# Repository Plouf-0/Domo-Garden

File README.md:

# Domo-Garden
#### A projet to add domotique in my garden

## 1. Project overview

#### Objective
Design and develop a Zigbee-based sensor network. The network will collect data from various environmental sensors (Thermal, Humidity, PH, ...), communicate wirelessly via Zigbee, and transmit data to a central hub that sends the information to a Home Assistant server via Wi-Fi. The system will also control an electrovalve based on predefined conditions.

#### Key Components:

- ESP32 + Zigbee module for Hub with Wi-Fi connectivity
- EFR32MG22-based sensor nodes
- Temperature, humidity sensors, and other IoT peripherals
- Electrovalve for irrigation control

## 2. Technical Specifications

#### Functional Requirements

    Data Collection: Periodic collection of temperature, humidity, and other sensor data.

    Communication: Use Zigbee for sensor node communication and Wi-Fi for sending data to the server.

    Control: Triggering of an electrovalve based on time or sensor data.

    Hub Features: The hub will aggregate data from up to 30 Zigbee devices and relay it via Wi-Fi to a server.

    Data Transfer Rate: Sensor data will be transmitted periodically, adjustable from 1 minute to 1 hour.

#### Hardware Specifications

    Microcontroller:
        ESP32
        EFR32MG22E224F512IM32

    Power Supply: Battery-powered nodes, possible use of solar panels. Minimum 1-month battery life without recharging. A 1000mAh = 1 year of battery life.

    Radio Frequency: Zigbee protocol.

    Communication Range: Up to 100 meters from hub, with a mesh network to cover distances up to 20 meters between each module.

    Sensors:
        Temperature sensors.
        Humidity sensors.
        Soil moisture sensors.
        Light sensors.
        PH sensors.
        More to come.

#### Software Specifications

    Programming Languages: C/C++ (for embedded systems), Python (for server-side automation).

    Development Environment: Simplicity Studio (for EFR32MG22).
    
    Protocols:
        Zigbee (3.0)
        Wi-Fi for hub (ESP32 or similar)
        MQTT (for data transmission to Home Assistant server).

    Operating System: FreeRTOS (for efficient power management).

#### Performance Metrics

    Battery Life: Minimum 30 days.

    Latency: Data transmission delay < 2 seconds between sensor reading and hub reception.

    Network Coverage: 100-meter total coverage using mesh networking.

## 3. Project Plan

#### Phases of Development

    Phase 1: Requirements Gathering & Research
        Gather requirements for sensors, control mechanisms, and networking.
        Research hardware options, compatibility with Zigbee and Home Assistant.

    Phase 2: Software Development
        Develop firmware for the EFR32MG22E224F512IM40 to read sensors, communicate via Zigbee, and send commands to the electrovalve with the EFR32xG22E Explorer Kit.
        Develop software for the Zigbee hub to manage data collection and Wi-Fi transmission to Home Assistant with the ESP32 and the Zigbee CC2530 Development Board.

    Phase 2^2: Hardware Design
        Design the PCB for sensor nodes (powered by EFR32MG22E224F512IM40).
        Create a schematic for power management (battery, solar charging).
        Select components for the electrovalve control system.
        Design and print the casing.

    Phase 3: Integration with Home Assistant
        Set up the Home Assistant server with Zigbee2MQTT or ZHA.
        Implement data visualization for sensor data.
        Test commands sent from Home Assistant to control the electrovalve.

    Phase 4: Prototyping
        Assemble and test initial sensor nodes and hub.
        Perform range and battery life tests.
        Ensure proper communication between the Zigbee nodes and the hub.

    Phase 6: Field Testing
        Deploy the system in a real environment (garden, yard).
        Monitor sensor performance, network stability, and control system reliability.

    Phase 6: Finalization & Documentation
        Finalize the design based on testing results.
        Prepare full documentation, including schematics, software, and user guide.

## 4. Risk Assessment

    Power Supply Issues: If solar panels are used, energy harvesting efficiency must be tested under various weather conditions.
    Connectivity Range: Trees and obstacles could interfere with Zigbee signals. Extensive field testing will be necessary to determine optimal node placement.
    Data Security: Implement encryption for data transmitted via Zigbee to prevent unauthorized access.
    Component Availability: Verify the supply chain for key components (e.g., EFR32MG22) to avoid potential delays due to shortages.

## 5. Additional Considerations

    OTA (Over-The-Air) Firmware Updates: Consider adding functionality for future remote firmware updates.
    Scalability: Keep flexibility in mind for expanding the network or adding more nodes later.

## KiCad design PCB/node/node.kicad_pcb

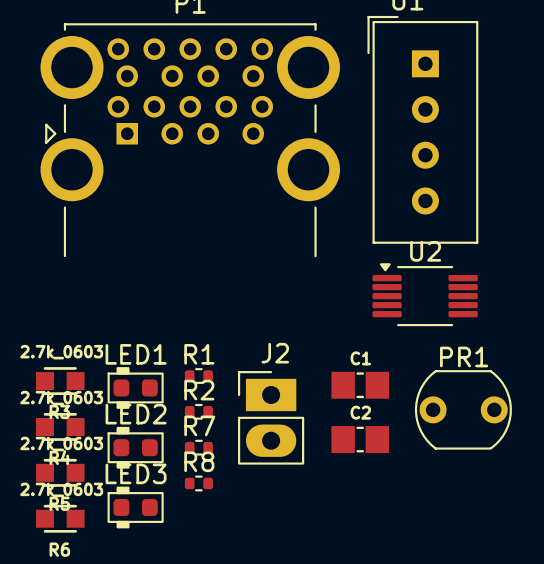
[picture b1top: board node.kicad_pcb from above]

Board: 2 copper layers, 18 parts (0 on the bottom side), 12 nets, no tracks yet.

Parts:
C1, C2: 10uF 6.3V; CAPC2012X70
J2: BATT; PinHeader_1x02_P2.54mm_Vertical
LED1: LED_0603_Green; LED_0603_1608Metric
LED2: LED_0603_Yellow; LED_0603_1608Metric
LED3: LED_0603_Red; LED_0603_1608Metric
P1: USB_C_Plug_USB2.0; USB3_A_Molex_48406-0001_Horizontal_Stacked
PR1: R_LDR_5.1x4.3mm_P3.4mm_Vertical
R1, R2, R7, R8: 10k_0402; R_0402_1005Metric
R3, R4, R5, R6: 2.7k_0603; R_0603
U1: DHT22; Aosong_DHT11_5.5x12.0_P2.54mm
U2: MCP73833-xxx-UN; MSOP-10_3x3mm_P0.5mm

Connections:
+3.3V: C2.1, J2.1, R1.1, R2.1, U1.1 (VDD), U2.9 (V_{BAT}), U2.10 (V_{BAT})
DHT GPIO: R1.2, U1.2 (DATA)
GND: C1.2, C2.2, J2.2, R6.2, R7.1, R8.1, U1.4 (GND), U2.5 (V_{SS})
unnamed: C1.1, LED1.2 (A), LED2.2 (A), LED3.2 (A), U2.1 (V_{DD}), U2.2 (V_{DD})
unnamed: LED1.1 (K), R3.1
unnamed: LED2.1 (K), R4.1
unnamed: LED3.1 (K), R5.1
unnamed: R6.1, R7.2, U2.6 (PROG)
unnamed: R4.2, U2.3 (STAT1)
unnamed: R3.2, U2.4 (STAT2)
unnamed: R8.2, U2.8 (THERM)
unnamed: R5.2, U2.7 (~PG)

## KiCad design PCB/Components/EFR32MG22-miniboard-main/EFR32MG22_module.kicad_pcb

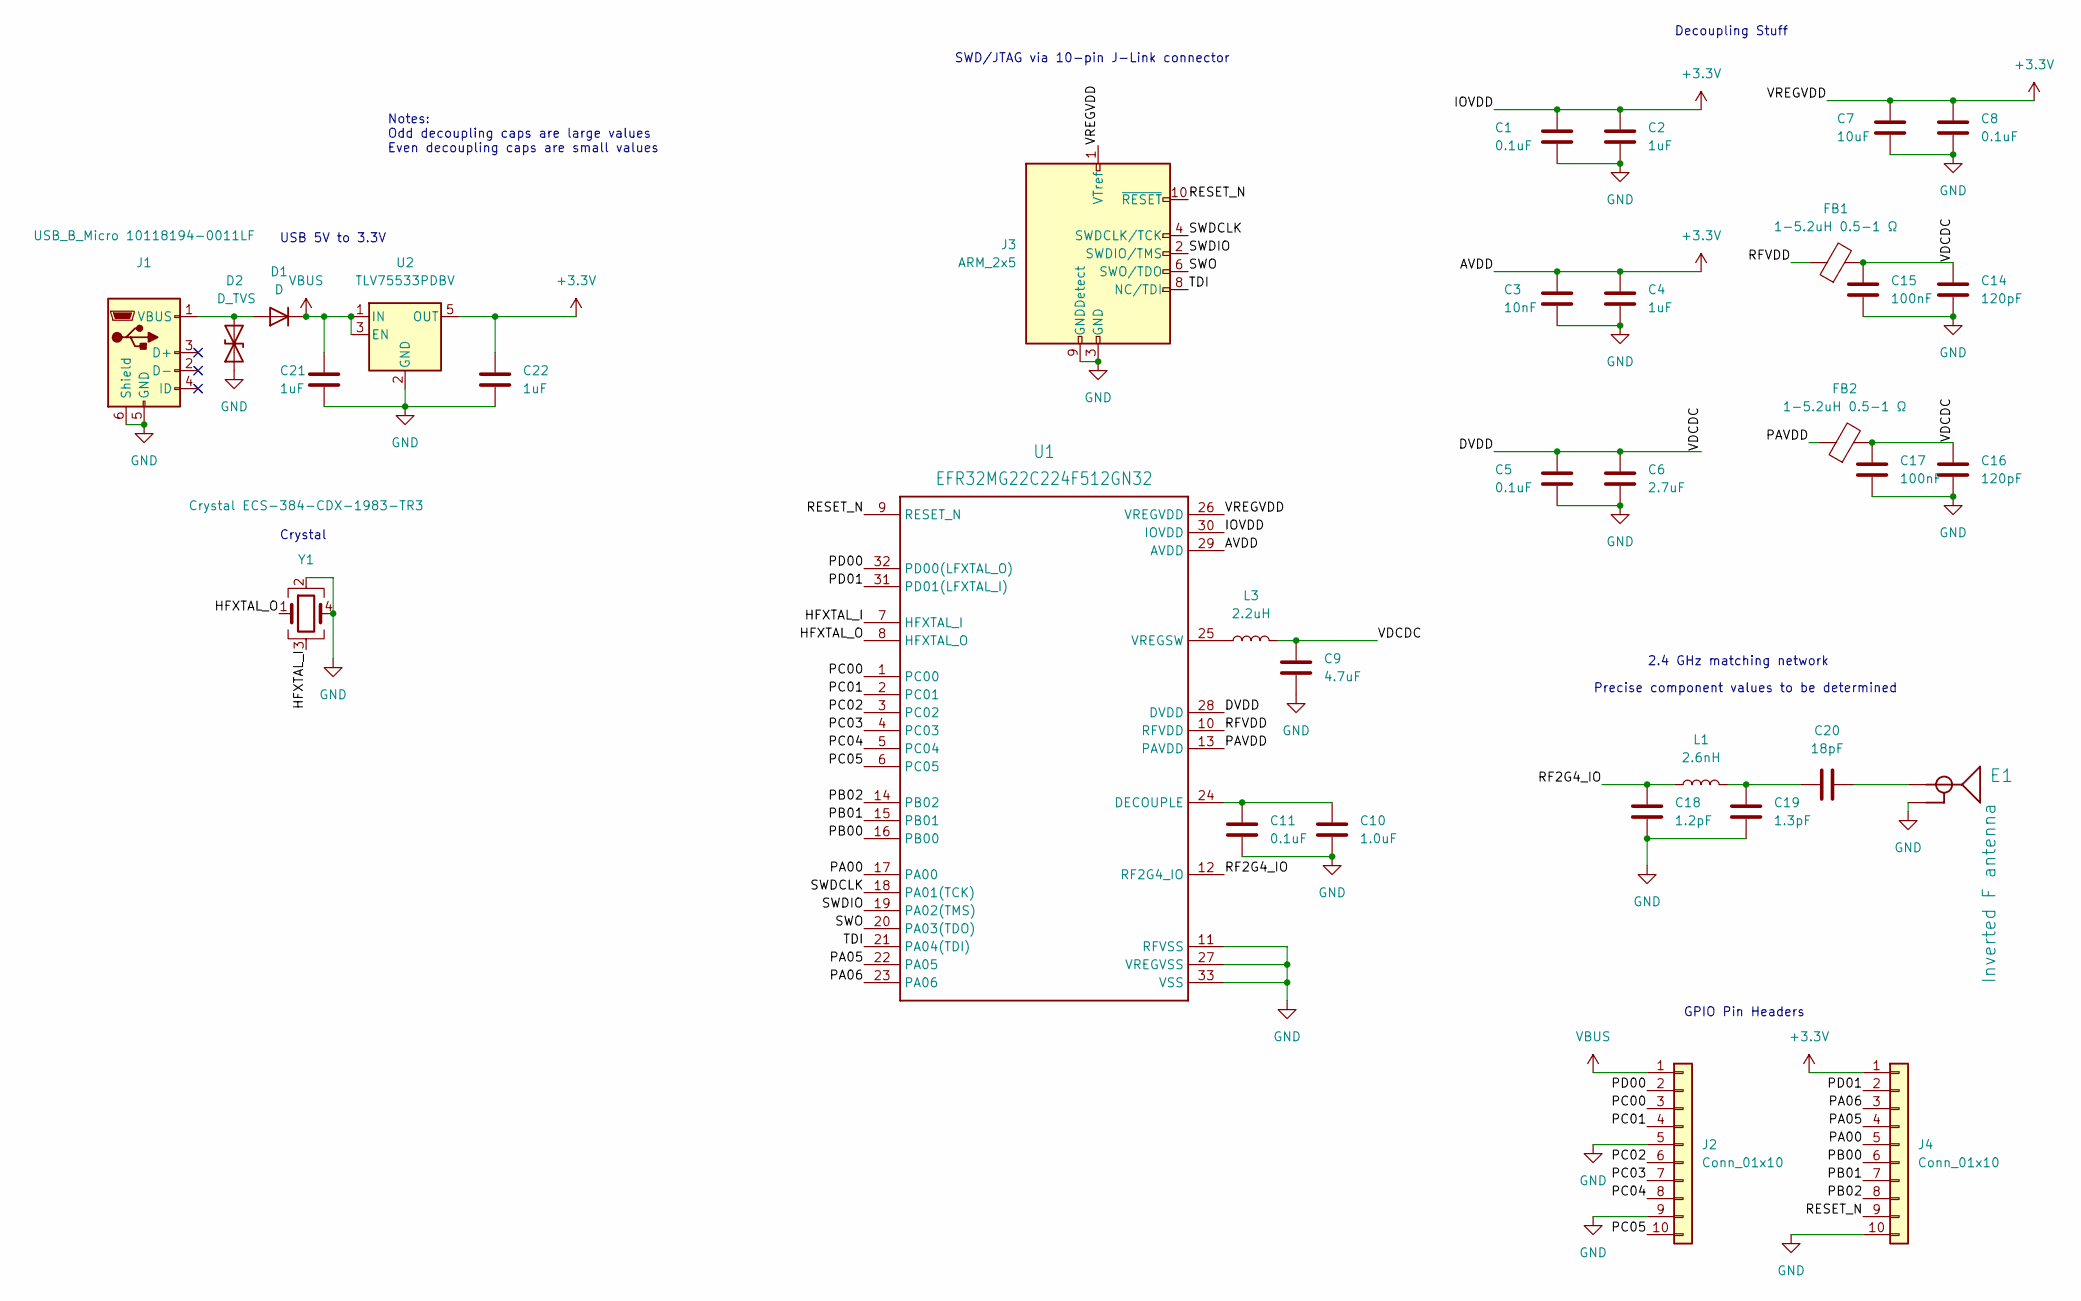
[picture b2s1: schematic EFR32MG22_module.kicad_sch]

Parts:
C1, C5, C8, C11: 0.1uF; C_0603_1608Metric_Pad1.08x0.95mm_HandSolder
C2, C4, C21, C22: 1uF; C_0603_1608Metric_Pad1.08x0.95mm_HandSolder
C3: 10nF; C_0603_1608Metric_Pad1.08x0.95mm_HandSolder
C6: 2.7uF; C_0603_1608Metric_Pad1.08x0.95mm_HandSolder
C7: 10uF; C_0603_1608Metric_Pad1.08x0.95mm_HandSolder
C9: 4.7uF; C_0603_1608Metric_Pad1.08x0.95mm_HandSolder
C10: 1.0uF; C_0603_1608Metric_Pad1.08x0.95mm_HandSolder
C14, C16: 120pF; C_0603_1608Metric_Pad1.08x0.95mm_HandSolder
C15, C17: 100nF; C_0603_1608Metric_Pad1.08x0.95mm_HandSolder
C18: 1.2pF; C_0603_1608Metric_Pad1.08x0.95mm_HandSolder
C19: 1.3pF; C_0603_1608Metric_Pad1.08x0.95mm_HandSolder
C20: 18pF; C_0603_1608Metric_Pad1.08x0.95mm_HandSolder
D1: D; D_SOD-123
D2: D_TVS; D_0201_0603Metric
E1: Inverted F antenna; TRACE_ANTENNA_2.4GHZ_15.2MM
FB1, FB2: 1-5.2uH 0.5-1 Ω; L_0603_1608Metric_Pad1.05x0.95mm_HandSolder
J1: USB_B_Micro 10118194-0011LF; USB_Micro-B_Amphenol_10118194_Horizontal
J2, J4: Conn_01x10; PinHeader_1x10_P2.54mm_Vertical
J3: ARM_2x5; 322010030000TR
L1: 2.6nH; L_0603_1608Metric_Pad1.05x0.95mm_HandSolder
L3: 2.2uH; L_0805_2012Metric_Pad1.15x1.40mm_HandSolder
U1: EFR32MG22C224F512GN32; QFN-32-1EP_4x4mm_P0.4mm_EP2.9x2.9mm_ThermalVias
U2: TLV75533PDBV; SOT-23-5
Y1: Crystal ECS-384-CDX-1983-TR3; Crystal_SMD_2016-4Pin_2.0x1.6mm

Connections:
+3.3V: C1.1, C2.1, C3.1, C4.1, C7.1, C8.1, C22.2, J3.1 (VTref), J4.1, U1.26 (VREGVDD), U1.29 (AVDD), U1.30 (IOVDD), U2.5 (OUT)
/DVDD: C5.1, C6.1, C9.1, C14.1, C15.1, C16.1, C17.1, FB1.2, FB2.2, L3.2, U1.28 (DVDD)
/HFXTAL_I: U1.7 (HFXTAL_I), Y1.3
/HFXTAL_O: U1.8 (HFXTAL_O), Y1.1
/PA00: J4.5, U1.17 (PA00)
/PA05: J4.4, U1.22 (PA05)
/PA06: J4.3, U1.23 (PA06)
/PAVDD: FB2.1, U1.13 (PAVDD)
/PB00: J4.6, U1.16 (PB00)
/PB01: J4.7, U1.15 (PB01)
/PB02: J4.8, U1.14 (PB02)
/PC00: J2.3, U1.1 (PC00)
/PC01: J2.4, U1.2 (PC01)
/PC02: J2.6, U1.3 (PC02)
/PC03: J2.7, U1.4 (PC03)
/PC04: J2.8, U1.5 (PC04)
/PC05: J2.10, U1.6 (PC05)
/PD00: J2.2, U1.32 (PD00(LFXTAL_O))
/PD01: J4.2, U1.31 (PD01(LFXTAL_I))
/RESET_N: J3.10 (~RESET), J4.9, U1.9 (RESET_N)
/RF2G4_IO: C18.1, L1.1, U1.12 (RF2G4_IO)
/RFVDD: FB1.1, U1.10 (RFVDD)
/SWDCLK: J3.4 (SWDCLK/TCK), U1.18 (PA01(TCK))
/SWDIO: J3.2 (SWDIO/TMS), U1.19 (PA02(TMS))
/SWO: J3.6 (SWO/TDO), U1.20 (PA03(TDO))
/TDI: J3.8 (NC/TDI), U1.21 (PA04(TDI))
GND: C1.2, C2.2, C3.2, C4.2, C5.2, C6.2, C7.2, C8.2, C9.2, C10.2, C11.2, C14.2, C15.2, C16.2, C17.2, C18.2, C19.2, C21.1, C22.1, D2.1 (A1), E1.GND, J1.5 (GND), J1.6 (Shield), J2.5, J2.9, J3.3 (GND), J3.5 (GND), J3.9 (GNDDetect), J4.10, U1.11 (RFVSS), U1.27 (VREGVSS), U1.33 (VSS), U2.2 (GND), Y1.2, Y1.4
unnamed: C10.1, C11.1, U1.24 (DECOUPLE)
unnamed: C19.1, C20.2, L1.2
unnamed: C20.1, E1.ANT (SIGNAL)
unnamed: D1.2 (A), D2.2 (A2), J1.1 (VBUS)
unnamed: L3.1, U1.25 (VREGSW)
VBUS: C21.2, D1.1 (K), J2.1, U2.1 (IN), U2.3 (EN)

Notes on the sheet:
GPIO Pin Headers
Precise component values to be determined
Notes: Odd decoupling caps are large values Even decoupling caps are small values
2.4 GHz matching network
SWD/JTAG via 10-pin J-Link connector
Crystal
Decoupling Stuff
USB 5V to 3.3V

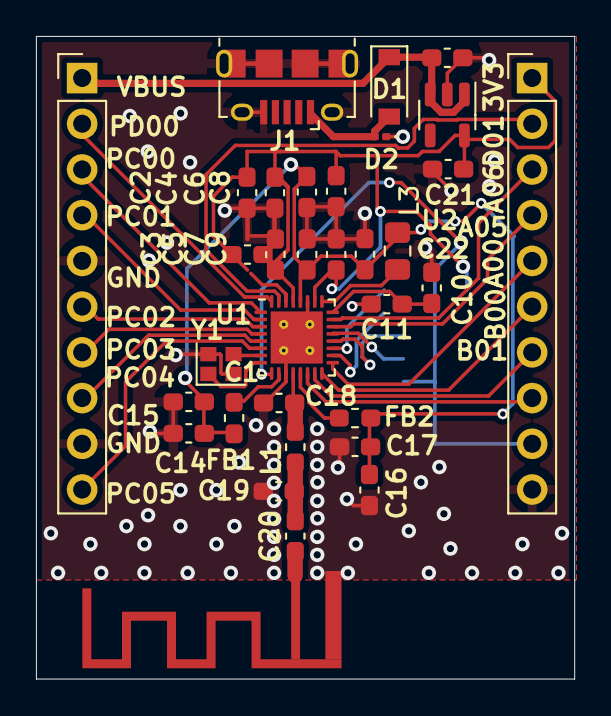
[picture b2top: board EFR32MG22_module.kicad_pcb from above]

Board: 2 copper layers, 29.9 x 35.7 mm, 34 parts (1 on the bottom side), 33 nets.

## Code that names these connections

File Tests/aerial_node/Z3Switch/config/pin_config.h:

#ifndef PIN_CONFIG_H
#define PIN_CONFIG_H

// $[CMU]
// [CMU]$

// $[LFXO]
// [LFXO]$

// $[PRS.ASYNCH0]
// [PRS.ASYNCH0]$

// $[PRS.ASYNCH1]
// [PRS.ASYNCH1]$

// $[PRS.ASYNCH2]
// [PRS.ASYNCH2]$

// $[PRS.ASYNCH3]
// [PRS.ASYNCH3]$

// $[PRS.ASYNCH4]
// [PRS.ASYNCH4]$

// $[PRS.ASYNCH5]
// [PRS.ASYNCH5]$

// $[PRS.ASYNCH6]
// [PRS.ASYNCH6]$

// $[PRS.ASYNCH7]
// [PRS.ASYNCH7]$

// $[PRS.ASYNCH8]
// [PRS.ASYNCH8]$

// $[PRS.ASYNCH9]
// [PRS.ASYNCH9]$

// $[PRS.ASYNCH10]
// [PRS.ASYNCH10]$

// $[PRS.ASYNCH11]
// [PRS.ASYNCH11]$

// $[PRS.SYNCH0]
// [PRS.SYNCH0]$

// $[PRS.SYNCH1]
// [PRS.SYNCH1]$

// $[PRS.SYNCH2]
// [PRS.SYNCH2]$

// $[PRS.SYNCH3]
// [PRS.SYNCH3]$

// $[GPIO]
// GPIO SWV on PA03
#ifndef GPIO_SWV_PORT                           
#define GPIO_SWV_PORT                            gpioPortA
#endif
#ifndef GPIO_SWV_PIN                            
#define GPIO_SWV_PIN                             3
#endif

// [GPIO]$

// $[TIMER0]
// [TIMER0]$

// $[TIMER1]
// [TIMER1]$

// $[TIMER2]
// [TIMER2]$

// $[TIMER3]
// [TIMER3]$

// $[TIMER4]
// [TIMER4]$

// $[USART0]
// [USART0]$

// $[USART1]
// [USART1]$

// $[I2C1]
// [I2C1]$

// $[PDM]
// [PDM]$

// $[LETIMER0]
// [LETIMER0]$

// $[IADC0]
// [IADC0]$

// $[I2C0]
// [I2C0]$

// $[EUART0]
// EUART0 CTS on PA08
#ifndef EUART0_CTS_PORT                         
#define EUART0_CTS_PORT                          gpioPortA
#endif
#ifndef EUART0_CTS_PIN                          
#define EUART0_CTS_PIN                           8
#endif

// EUART0 RTS on PA07
#ifndef EUART0_RTS_PORT                         
#define EUART0_RTS_PORT                          gpioPortA
#endif
#ifndef EUART0_RTS_PIN                          
#define EUART0_RTS_PIN                           7
#endif

// EUART0 RX on PA06
#ifndef EUART0_RX_PORT                          
#define EUART0_RX_PORT                           gpioPortA
#endif
#ifndef EUART0_RX_PIN                           
#define EUART0_RX_PIN                            6
#endif

// EUART0 TX on PA05
#ifndef EUART0_TX_PORT                          
#define EUART0_TX_PORT                           gpioPortA
#endif
#ifndef EUART0_TX_PIN                           
#define EUART0_TX_PIN                            5
#endif

// [EUART0]$

// $[PTI]
// PTI DFRAME on PC05
#ifndef PTI_DFRAME_PORT                         
#define PTI_DFRAME_PORT                          gpioPortC
#endif
#ifndef PTI_DFRAME_PIN                          
#define PTI_DFRAME_PIN                           5
#endif

// PTI DOUT on PC04
#ifndef PTI_DOUT_PORT                           
#define PTI_DOUT_PORT                            gpioPortC
#endif
#ifndef PTI_DOUT_PIN                            
#define PTI_DOUT_PIN                             4
#endif

// [PTI]$

// $[MODEM]
// [MODEM]$

// $[CUSTOM_PIN_NAME]
#ifndef _PORT                                   
#define _PORT                                    gpioPortA
#endif
#ifndef _PIN                                    
#define _PIN                                     0
#endif

// [CUSTOM_PIN_NAME]$

#endif // PIN_CONFIG_H

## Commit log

2024-09-10 udate readme
2024-09-12 init PCB project
2024-09-20 update pcb
2024-09-29 change to add jlink
2024-10-15 tests_efr
2024-10-22 creation tests
2024-10-22 add tests
